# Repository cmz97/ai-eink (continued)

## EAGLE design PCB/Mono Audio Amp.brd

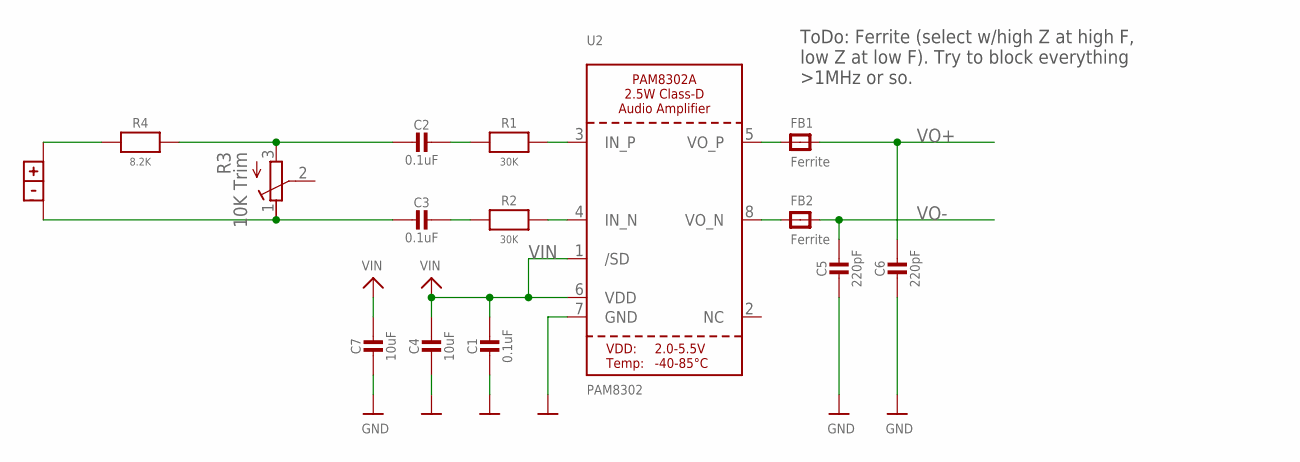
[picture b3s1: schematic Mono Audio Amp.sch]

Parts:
C1, C2, C3: 0.1uF; 0603-NO
C4, C7: 10uF; 0805-NO
C5, C6: 220pF; 0603-NO
FB1, FB2: Ferrite; 0603-NO
LS1: CMS-18138A-SP; CUI_CMS-18138A-SP
R1, R2: 30K; 0603-NO
R3: 10K Trim; RTRIM3314J
R4: 8.2K; 0603-NO
U2: PAM8302; MSOP8_0.65MM

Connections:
GND: C1.2, C4.2, C5.2, C6.2, C7.2, U2.7 (GND)
IN+: R1.2, U2.3 (IN_P)
IN-: R2.2, U2.4 (IN_N)
unnamed: C3.2, LS1.N, R3.1 (E)
unnamed: LS1.P, R4.1
unnamed: C3.1, R2.1
unnamed: C2.1, R1.1
unnamed: C2.2, R3.3 (A), R4.2
OUT+: FB1.1, U2.5 (VO_P)
OUT-: FB2.1, U2.8 (VO_N)
VIN: C1.1, C4.1, C7.1, U2.1 (/SD), U2.6 (VDD)
VO+: C6.1, FB1.2
VO-: C5.1, FB2.2

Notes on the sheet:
ToDo: Ferrite (select w/high Z at high F, low Z at low F). Try to block everything >1MHz or so.

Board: 2 copper layers, 15 parts (0 on the bottom side), 13 nets, no tracks yet.

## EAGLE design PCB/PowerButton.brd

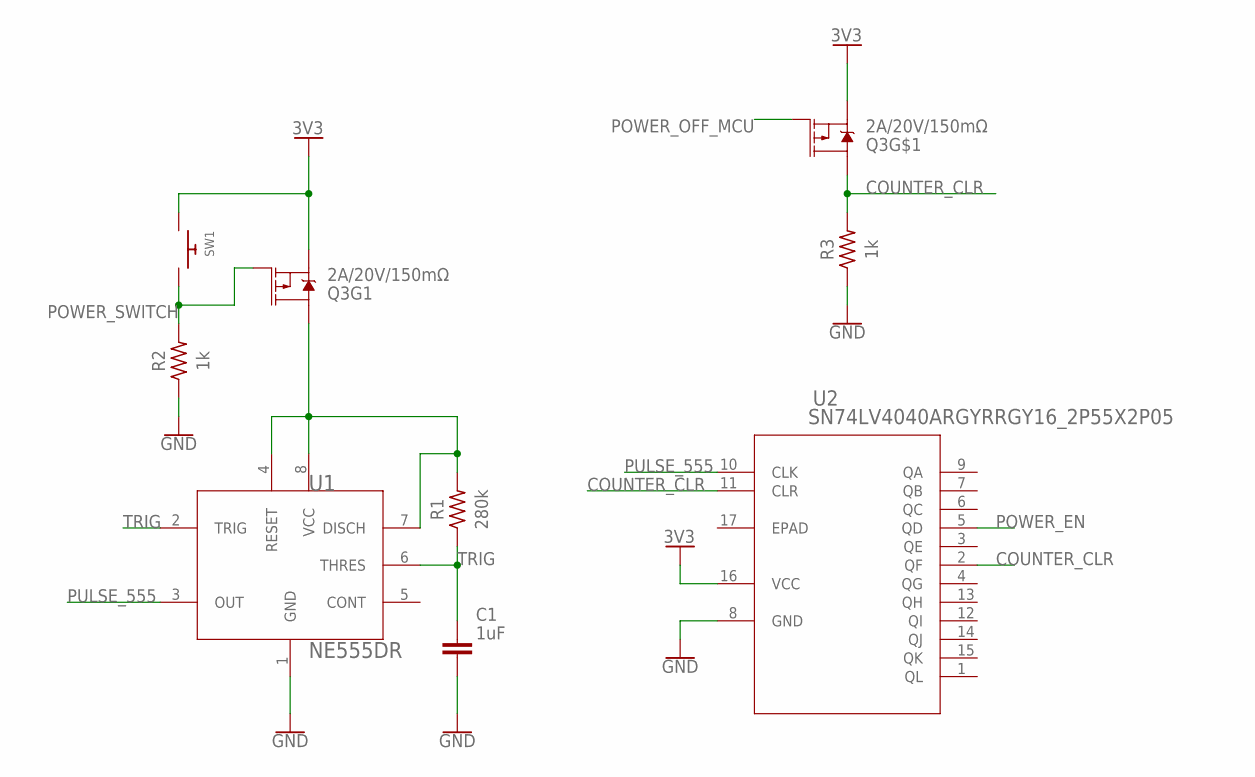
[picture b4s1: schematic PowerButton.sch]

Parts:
C1: 1uF; CAPC1608X85
Q3: 2A/20V/150mΩ; SOT26
R1: 280k; RESC1608X60
R2, R3: 1k; RESC1608X60
SW1: SWITCH_PUSHBUTTONSOFTTOUCHSMD_SJ; PUSHBUTTON_SMD_SJ
U1: NE555DR; SOIC-8N
U2: SN74LV4040ARGYRRGY16_2P55X2P05; RGY16_2P55X2P05

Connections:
3V3: Q3.S1 (S), Q3.S2 (S), SW1.P$1, U2.16 (VCC)
COUNTER_CLR: Q3.D2 (D), R3.2, U2.2 (QF), U2.11 (CLR)
GND: C1.2, R2.1, R3.1, U1.1 (GND), U2.8 (GND)
unnamed: Q3.D1 (D), R1.2, U1.4 (RESET), U1.7 (DISCH), U1.8 (VCC)
POWER_EN: U2.5 (QD)
POWER_OFF_MCU: Q3.G2 (G)
POWER_SWITCH: Q3.G1 (G), R2.2, SW1.P$2
PULSE_555: U1.3 (OUT), U2.10 (CLK)
TRIG: C1.1, R1.1, U1.2 (TRIG), U1.6 (THRES)

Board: 2 copper layers, 8 parts (0 on the bottom side), 7 nets, no tracks yet.

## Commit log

2024-02-17 init
2024-02-17 updated main with better llm prompt and sd prompt
2024-02-17 bruh
2024-02-17 bruh2
2024-02-18 skip chat and reduce sd step to 1
2024-02-21 added PCB
2024-02-21 added mic interface and RFID
2024-03-02 ditering
2024-03-02 change stuff
2024-03-03 folder struct change
2024-03-03 added testing script
2024-03-03 adhoc
2024-03-03 random fix
2024-03-03 switch random to np
2024-03-03 added vae tiling
2024-03-03 from pi
2024-03-03 vae wrapper back to in8
2024-03-04 enable llm
2024-03-04 keep llm alive
2024-03-04 remove llm json api option
2024-03-04 added interface
2024-03-04 added apps file
2024-03-04 bug fix
2024-03-04 stable version
2024-03-07 big sync
2024-03-07 sync
2024-03-07 stable release 2024.0307
2024-03-10 sync up
2024-03-10 updaet
2024-03-10 added loading screen + stable version
2024-03-10 stable
2024-03-12 stable version 0311
2024-03-14 update install requirements
2024-03-14 minor update
2024-03-15 update ui button color
2024-03-17 update ui
2024-03-17 stable version, slow for some reason
2024-03-17 added fav
2024-03-23 stable version 0323
2024-03-27 pcb before downsize
2024-03-28 stable version ebook
2024-03-28 kevin commit
2024-03-30 added tamagochi model
2024-03-30 udpate
2024-03-30 PCB V3
2024-03-30 stsable tamagotchi
2024-03-30 unstable
2024-03-31 update animation image
2024-03-31 tama stable
2024-04-04 pcb v4
2024-04-04 stable version + cam demo
2024-04-10 GUI done
2024-04-11 stable kid book
2024-04-11 home page test
2024-04-11 update kid book UI
2024-04-11 ebook ui update stable
2024-04-13 stable demo version
2024-04-13 stable ver.0 for demo
2024-04-14 stable demo ver0.2
2024-04-15 stable demo ver.stable
2024-04-15 added asciiTable.png
2024-04-17 add sam code
2024-04-19 update camtest
2024-04-20 stable RAG
2024-04-21 ver2 stable
2024-04-21 added mic test, stable
2024-04-22 update button
2024-04-23 stable mic
2024-04-23 mic stable
2024-04-25 v5 PCB done
2024-04-25 stable cam
2024-05-01 Break
2024-05-01 Create
2024-05-01 einkDSP support rock
2024-05-01 move asset
2024-05-06 cm5 rock eink driver integration
2024-06-20 v0.7
2024-07-02 before modification, v0.7, for fateen and adam
2024-08-05 ESP32
